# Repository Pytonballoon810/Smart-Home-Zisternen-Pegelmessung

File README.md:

# Zisternen-Pegelmessung

Continuous water level measurement for a garden cistern, using a hydrostatic
4–20 mA probe read by an ESP8266 and reported to Home Assistant via ESPHome.

Replaces a ten-contact float ladder that resolved 300 litres per step — too
coarse to answer the question that actually matters: *is there enough water for
tomorrow's irrigation, and how fast does the tank recover?*

---

## How it works

A 2-wire loop-powered probe sits near the bottom of the shaft and pushes 4 mA
when the water column is zero, 20 mA at full range. That current runs through a
100 Ω burden resistor, turning it into 0.400 V … 2.000 V, which a 16-bit
ADS1115 reads over I²C. ESPHome converts volts to centimetres, then to litres.

The reason for 4–20 mA rather than a voltage output: **a broken cable reads
0 mA, which is 0.000 V — clearly distinguishable from an empty tank at 4 mA.**
A voltage sensor cannot tell those apart, and a cistern that reports "empty"
because a mouse chewed the cable is worse than no sensor at all.

| State | Current | Voltage |
|---|--:|--:|
| Cable break | 0 mA | 0.00 V |
| Empty | 4 mA | 0.40 V |
| Full | 20 mA | 2.00 V |
| Short / overrange | 30 mA | 3.00 V |

---

## Repository layout

| Path | Contents |
|---|---|
| [`docs/hardware.md`](docs/hardware.md) | Bill of materials, wiring, how to choose a probe, installation in the shaft |
| [`docs/pcb-specification.md`](docs/pcb-specification.md) | Interface board: circuit, rationale, v1.0 → v1.1 change log |
| [`docs/calibration.md`](docs/calibration.md) | Two-point calibration procedure — **do not skip this** |
| [`docs/home-assistant.md`](docs/home-assistant.md) | Entities, dashboard cards, derived sensors, automations |
| [`docs/findings.md`](docs/findings.md) | Measured behaviour of an open-bottomed cistern |
| [`esphome/`](esphome/) | Device configuration and secrets template |
| [`hardware/`](hardware/) | KiCAD project, custom libraries, fabrication outputs |
| [`images/`](images/) | Photographs (shot list only — nothing built yet) |

---

## Status

| Part | State |
|---|---|
| ESPHome configuration | Written, not yet flashed |
| Interface PCB | Designed, routed, ERC/DRC clean — **not yet fabricated** |
| Probe and installation | Not yet purchased or built |
| Calibration | Pending installation |

Nothing here has been through a full build yet. The findings in
[`docs/findings.md`](docs/findings.md) come from the float ladder this project
replaces, not from the probe.

---

## Before you build one of these

**Get a vented probe.** The cable must contain a capillary venting the sensor
to atmosphere. Without it the probe measures water column *plus* barometric
pressure, and a normal weather system moves that by 20–30 cm of apparent water
— hundreds of litres of error that drifts rather than breaks. This is the single
most expensive mistake available here.

**The burden resistor sets your accuracy.** 100 Ω at 0.1 % and ≤50 ppm/K. A 1 %
part dominates every other error in the chain, including the probe's own.

**Calibrate in two points after installation.** The shipped transfer curve is
theoretical. Ten minutes with a multimeter and a tape measure is the difference
between an indication and a measurement.

**The v1.1 board has no input protection.** No fuse, no reverse-polarity diode,
no TVS — deliberately, to keep the part count at eight. Feed it from a
known-good supply and check polarity at J1. See §14 of the PCB specification
for what to reinstate if your installation is less forgiving than a dry shed.

---

## An honest caveat about open-bottomed cisterns

This cistern has an open bottom, in hydraulic contact with groundwater. That
makes it a **buffer, not a reservoir**: the level settles at the groundwater
table, rainfall above that drains away within hours, and the tank refills itself
after heavy draw-off. Measured recovery was roughly 600 litres in five hours.

The practical consequence is that usable storage is not the tank volume but the
gap between groundwater level and full — and that gap moves with the season, so
a fixed "ration below X litres" rule does not work.

[`docs/findings.md`](docs/findings.md) has the measurements. If your cistern is
sealed, none of it applies.

Groundwater abstraction is also regulated in most jurisdictions — in Germany
under the Wasserhaushaltsgesetz. Worth asking your local authority before
building something similar.

---

## Licence

Not yet chosen. Until one is added, treat this as "look, learn, but ask before
redistributing".

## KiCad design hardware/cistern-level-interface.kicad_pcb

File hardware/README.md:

# KiCAD project

The interface board itself. **The design is documented in
[`../docs/pcb-specification.md`](../docs/pcb-specification.md)** — circuit,
BOM, rationale and the v1.0 → v1.1 change log. This file covers only the
mechanics of working with the KiCAD project.

## Status

| Stage | State |
|---|---|
| Schematic | ERC **0 errors, 0 warnings** |
| Netlist | Verified against intent (8 nets) |
| Placement | No courtyard overlaps |
| Routing | 68 segments, 6 vias, **0 unconnected** |
| DRC | **0 errors** (5 cosmetic silkscreen warnings) |
| Fabrication outputs | Gerbers, drill, BOM, PDFs in `output/` |

The silkscreen warnings are U2's outline crossing the board edge, which is the
deliberate antenna overhang, plus reference designators overlapping the
connector labels.

## Layout

```
hardware/
  cistern-level-interface.kicad_pro   project (also carries the DRC floor)
  cistern-level-interface.kicad_sch   schematic
  cistern-level-interface.kicad_pcb   board
  fp-lib-table, sym-lib-table         point at lib/ — needed for the custom parts
  lib/cistern.kicad_sym               ADS1115_Breakout, MP1584_Module symbols
  lib/cistern.pretty/                 MP1584EN_Buck_Module footprint
  output/                             generated: Gerbers, drill, BOM, PDFs, render
```

`lib/cistern.pretty/Fuse_Bourns_MF-R025_Radial.kicad_mod` is unused in v1.1. It
is kept because the protected variant in the change log would need it.

## Custom parts

Both module footprints were built from the physical hardware, not datasheets:

- **MP1584EN** — 22.3 × 16.8 mm, four corner connections each doubled on
  2.54 mm pitch (8 holes), columns 19.05 mm apart. Top view: IN left, OUT
  right, `+` is the lower hole of each pair. Pad pitch still wants a caliper
  check before ordering.
- **ADS1115 (KY-053)** — plain 1×10 header on 2.54 mm, order VDD, GND, SCL,
  SDA, ADDR, ALRT, A0, A1, A2, A3. Confirmed against the module.

## Regenerating outputs

```bash
kicad-cli sch export pdf -o output/cistern-level-interface-schematic.pdf cistern-level-interface.kicad_sch
kicad-cli pcb export gerbers -o output/gerbers cistern-level-interface.kicad_pcb
kicad-cli pcb export drill -o output/gerbers/ cistern-level-interface.kicad_pcb
kicad-cli pcb drc --severity-error cistern-level-interface.kicad_pcb
```

## Re-routing

Routed with the [KiCADRoutingTools](https://github.com/drandyhaas/kicadroutingtools)
plugin, headless:

```bash
python route.py in.kicad_pcb out.kicad_pcb --layers F.Cu B.Cu --clearance 0.2 --track-width 0.25 --via-size 0.6 --via-drill 0.3 --power-nets "*GND*" "*19V*" "*5V*" "*3V3*" --power-nets-widths 0.8 0.8 0.5 0.5
```

Two rules from the plugin's own docs that are easy to get wrong:

- Copy boards with its `copy_board.py`, not `cp`. A bare copy strands the
  sibling `.kicad_pro` that carries the DRC floor, and KiCAD then grades
  correct copper as phantom violations.
- Route to a **fresh** output path each run. Re-using one makes `route.py` read
  back its own `.kicad_pro` and silently change the result.

Verify with all three — they check different things:

```bash
python check_connected.py out.kicad_pcb
python check_drc.py out.kicad_pcb --clearance 0.2 --clearance-margin 0.1
kicad-cli pcb drc --severity-error out.kicad_pcb
```

A DRC-clean board can be entirely disconnected; isolated copper has no
clearance conflicts.

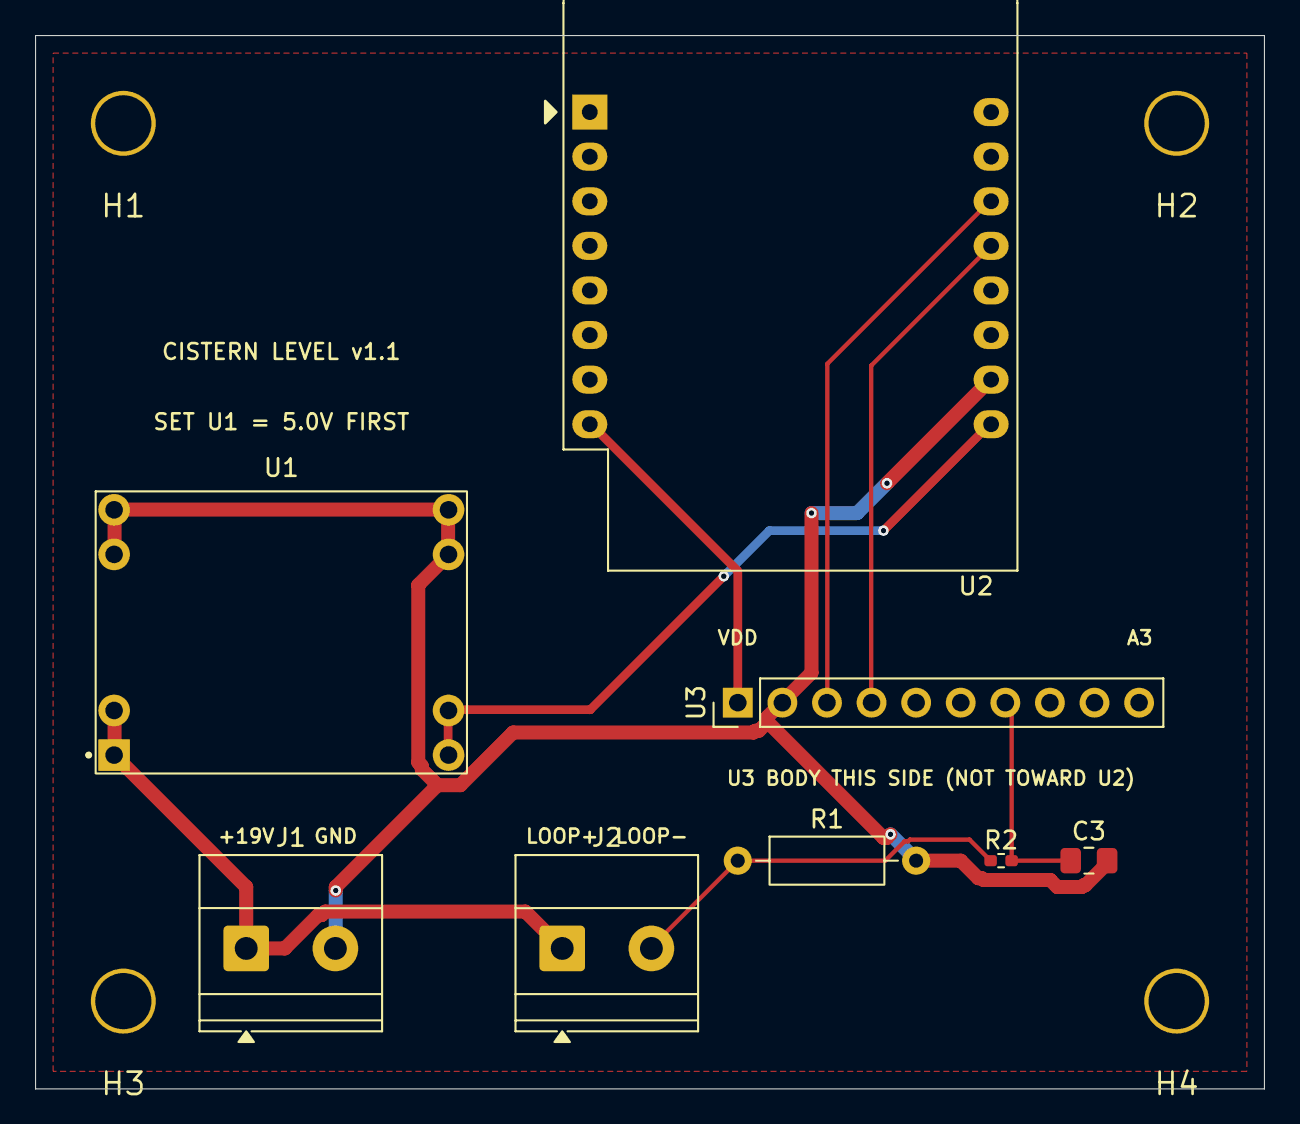
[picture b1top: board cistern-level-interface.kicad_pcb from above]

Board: 2 copper layers, 70.0 x 60.0 mm, 12 parts (0 on the bottom side), 8 nets.

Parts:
C3: C_0805_2012Metric_Pad1.18x1.45mm_HandSolder
H1, H2, H3, H4: MountingHole; MountingHole_3.2mm
J1, J2: TerminalBlock_Phoenix_MKDS-1,5-2-5.08_1x02_P5.08m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; TerminalBlock_Phoenix_MKDS-1,5-2-5.08_1x02_P5.08mm_Horizont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
R1: R_Axial_DIN0207_L6.3mm_D2.5mm_P10.16mm_Horizontal
R2: R_0402_1005Metric_Pad0.72x0.64mm_HandSolder
U1: MP1584EN_Buck_Module
U2: WEMOS_D1_mini_light
U3: PinHeader_1x10_P2.54mm_Vertical

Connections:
+3V3: U2.8, U3.1
+5V: U1.3, U2.9
/+19V: J1.1, J2.1, U1.1
/ADC_A0: C3.1, R2.2, U3.7
/I_SENSE: J2.2, R1.1, R2.1
/SCL: U2.14, U3.3
/SDA: U2.13, U3.4
GND: C3.2, J1.2, R1.2, U1.2, U1.4, U2.10, U3.2
